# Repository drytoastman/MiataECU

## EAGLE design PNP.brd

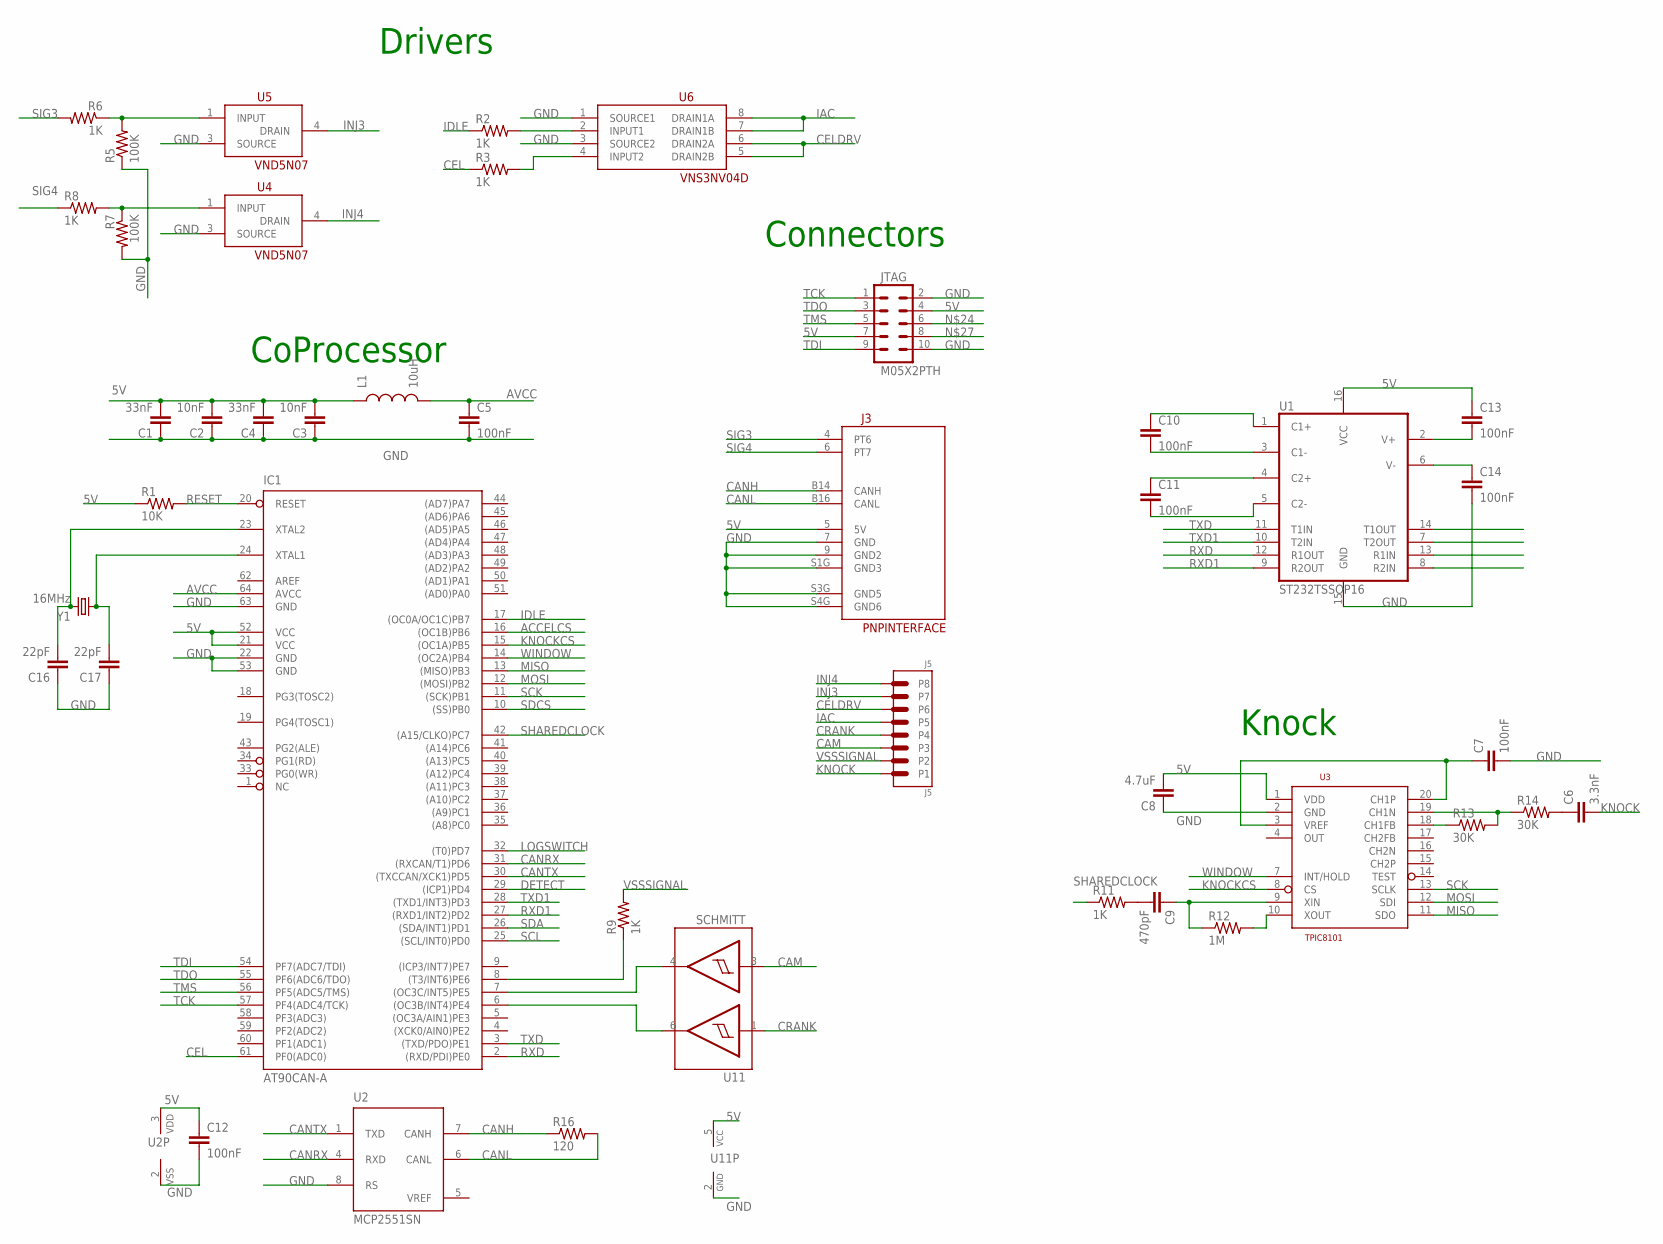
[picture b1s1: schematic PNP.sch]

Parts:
C1, C4: 33nF; 0805
C2, C3: 10nF; 0805
C5, C7, C10, C11, C12, C13, C14: 100nF; 0805
C6: 3.3nF; 0805
C8: 4.7uF; 0805
C9: 470pF; 0805
C16, C17: 22pF; 0805
IC1: AT90CAN-A; TQFP64
J3: PNPINTERFACE; PNPBOARD
J5: J5; TERMINAL8
JTAG: M05X2PTH; AVR_ICSP
L1: 10uH; 1210
R1: 10K; 0805
R2, R3, R6, R8, R9, R11: 1K; 0805
R5, R7: 100K; 0805
R12: 1M; 0805
R13, R14: 30K; 0805
R16: 120; 0805
U1: ST232TSSOP16; TSSOP16
U2: MCP2551SN; SO8
U3: TPIC8101; SO-20DW
U4, U5: VND5N07; DPAK
U6: VNS3NV04D; SO8
U11: SCHMITT; TSOP6
Y1: 16MHz; SM2-CRYSTAL-7ASERIES

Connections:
5V: C1.2, C2.2, C3.2, C4.2, C8.2, C12.1, C13.1, IC1.21 (VCC), IC1.52 (VCC), J3.5 (5V), JTAG.4, JTAG.7, L1.1, R1.1, U1.16 (VCC), U2.3 (VDD), U3.1 (VDD), U11.5 (VCC)
ACCELCS: IC1.16 ((OC1B)PB6)
AVCC: C5.1, IC1.64 (AVCC), L1.2
CAM: J5.P3, U11.3 (I2)
CANH: J3.B14 (CANH), R16.1, U2.7 (CANH)
CANL: J3.B16 (CANL), R16.2, U2.6 (CANL)
CANRX: IC1.31 ((RXCAN/T1)PD6), U2.4 (RXD)
CANTX: IC1.30 ((TXCCAN/XCK1)PD5), U2.1 (TXD)
CEL: IC1.61 (PF0(ADC0)), R3.1
CELDRV: J5.P6, U6.5 (DRAIN2B), U6.6 (DRAIN2A)
CRANK: J5.P4, U11.1 (I1)
DETECT: IC1.29 ((ICP1)PD4)
GND: C1.1, C2.1, C3.1, C4.1, C5.2, C7.2, C8.1, C12.2, C14.2, C16.1, C17.1, IC1.22 (GND), IC1.53 (GND), IC1.63 (GND), J3.7 (GND), J3.9 (GND2), J3.S1G (GND3), J3.S3G (GND5), J3.S4G (GND6), JTAG.2, JTAG.10, R5.1, R7.2, U1.15 (GND), U2.2 (VSS), U2.8 (RS), U3.2 (GND), U4.3 (SOURCE), U5.3 (SOURCE), U6.1 (SOURCE1), U6.3 (SOURCE2), U11.2 (GND)
IAC: J5.P5, U6.7 (DRAIN1B), U6.8 (DRAIN1A)
IDLE: IC1.17 ((OC0A/OC1C)PB7), R2.1
INJ3: J5.P7, U5.4 (DRAIN)
INJ4: J5.P8, U4.4 (DRAIN)
KNOCK: C6.2, J5.P1
KNOCKCS: IC1.15 ((OC1A)PB5), U3.8 (CS)
LOGSWITCH: IC1.32 ((T0)PD7)
MISO: IC1.13 ((MISO)PB3), U3.11 (SDO)
MOSI: IC1.12 ((MOSI)PB2), U3.12 (SDI)
unnamed: C6.1, R14.2
unnamed: R5.2, R6.1, U5.1 (INPUT)
unnamed: IC1.7 ((OC3C/INT5)PE5), U11.4 (O2)
unnamed: IC1.6 ((OC3B/INT4)PE4), U11.6 (O1)
unnamed: R2.2, U6.2 (INPUT1)
unnamed: C9.2, R11.2
unnamed: R3.2, U6.4 (INPUT2)
unnamed: R7.1, R8.2, U4.1 (INPUT)
unnamed: C10.1, U1.1 (C1+)
unnamed: C10.2, U1.3 (C1-)
unnamed: IC1.8 ((T3/INT6)PE6), R9.1
unnamed: C9.1, R12.1, U3.9 (XIN)
unnamed: C11.1, U1.4 (C2+)
unnamed: R12.2, U3.10 (XOUT)
unnamed: C16.2, IC1.23 (XTAL2), Y1.P$2 (2)
unnamed: C17.2, IC1.24 (XTAL1), Y1.P$1 (1)
unnamed: C11.2, U1.5 (C2-)
unnamed: C7.1, U3.3 (VREF), U3.20 (CH1P)
unnamed: C13.2, U1.2 (V+)
unnamed: C14.1, U1.6 (V-)
unnamed: R13.2, R14.1, U3.19 (CH1N)
unnamed: R13.1, U3.18 (CH1FB)
RESET: IC1.20 (RESET), R1.2
RXD: IC1.2 ((RXD/PDI)PE0), U1.12 (R1OUT)
RXD1: IC1.27 ((RXD1/INT2)PD2), U1.9 (R2OUT)
SCK: IC1.11 ((SCK)PB1), U3.13 (SCLK)
SCL: IC1.25 ((SCL/INT0)PD0)
SDA: IC1.26 ((SDA/INT1)PD1)
SDCS: IC1.10 ((SS)PB0)
SHAREDCLOCK: IC1.42 ((A15/CLKO)PC7), R11.1
SIG3: J3.4 (PT6), R6.2
SIG4: J3.6 (PT7), R8.1
TCK: IC1.57 (PF4(ADC4/TCK)), JTAG.1
TDI: IC1.54 (PF7(ADC7/TDI)), JTAG.9
TDO: IC1.55 (PF6(ADC6/TDO)), JTAG.3
TMS: IC1.56 (PF5(ADC5/TMS)), JTAG.5
TXD: IC1.3 ((TXD/PDO)PE1), U1.11 (T1IN)
TXD1: IC1.28 ((TXD1/INT3)PD3), U1.10 (T2IN)
VSSSIGNAL: J5.P2, R9.2
WINDOW: IC1.14 ((OC2A)PB4), U3.7 (INT/HOLD)

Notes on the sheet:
Drivers
Knock
Connectors
CoProcessor

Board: 2 copper layers, 42 parts (0 on the bottom side), 56 nets, no tracks yet.

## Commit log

2011-10-15 base files
2011-10-15 progress
2011-10-16 more progress at first version
2011-10-17 move to PH board mounting
2011-10-17 add power supply, remove some unecessary stuff
2011-10-19 move to power supply from MS V3 board
2011-10-19 go for mosfet SMD to remove excess components
2011-10-20 after backport of footprints
2011-10-20 perhaps done with the schematic portion, hopefully
2011-10-20 reorg directory as coprocessor components will go on their own board
2011-10-20 fix up for new arrangement
2011-10-20 from outside doc folder
2011-10-22 save point
2011-10-22 move coproc back onto mainboard to save PCB material
2011-10-25 remove old coproc dir, looking at alternator circuits
2011-10-26 bring back injector driver onto main board
2011-10-26 fix ups for drivers and tests import into board
2011-10-26 forget flyback
2011-10-29 more work, split complexity into more sheets
2011-10-29 use 'isolator' for accel circuit and ISP protection
2011-10-31 starting some board layout, need to double check footprints, some where wonky
2011-11-02 lots of stuff and board busing
2011-11-02 temp commit, changing direction yet again
2011-11-04 moved back to eagle, going for small single board addon rather than redoing entire board
2011-11-05 save status as I'm going to dump the alternator control
2011-11-06 seemingly finalized schematic, starting layout
2011-11-07 an actual routed board
2011-11-07 some cleanup and labelling updates
2011-11-07 add cam file for output
2011-11-08 why not add a battery backed up RTC
2011-11-08 enlarge and put battery on board
2011-11-08 some more last tweaks
2011-11-10 label cleanup
2011-11-11 couple part details, bigger caps around microSD socket for card insertion, swap to bidi MAX3378 as 3392 is not in stock anywhere
2011-11-12 cleanup, move old files out of the way for now
2011-11-12 establish base AVR project
2011-11-13 initial pffs lib and base mcc code
2011-11-16 drop fat lib support and just do it ourselves
2011-11-16 get cluster search working
2011-11-16 dumping Studio5
2011-11-16 move back to Studio4, so much faster
2011-11-18 start filling in other pieces
2011-11-19 update board for changes including CAM/CRANK input or lots of minor things
2011-11-20 more layout work
2011-11-20 yet more layout adjustments
2011-11-21 little changes as we update the bom
2012-02-27 saving some things before a move
2012-03-14 none
2012-04-09 some hacking on the can bus part
2012-04-18 save progress in getting fimrware working, canbus works, idle output seems okay, setting SCK to output handings JTAG debugging session though so can't test knock sensor SPI interface yet
2012-04-18 SPI appears to work now that defunct level converter chip is removed (no 3.3V on board right now)
2012-04-21 add ini and integrate with TunerStudio, store config in eeprom
2012-04-22 better integration with TunerStudio, now set things like the knock sensor config values as well
2012-05-17 work on knock sensor inputs, controls and general debugging
2012-07-08 start removing unused pieces
2016-11-13 opened with latest eagle, also have some changes still floating on my system at home, commit them all so I remove the local copy

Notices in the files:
parts and their libraries:
SparkFun: Licensing: CC v3.0 Share-Alike You are welcome to use this library for commercial purposes.
